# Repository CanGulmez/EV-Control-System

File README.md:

# EV Control System based on BBB (BeagleBone Black)

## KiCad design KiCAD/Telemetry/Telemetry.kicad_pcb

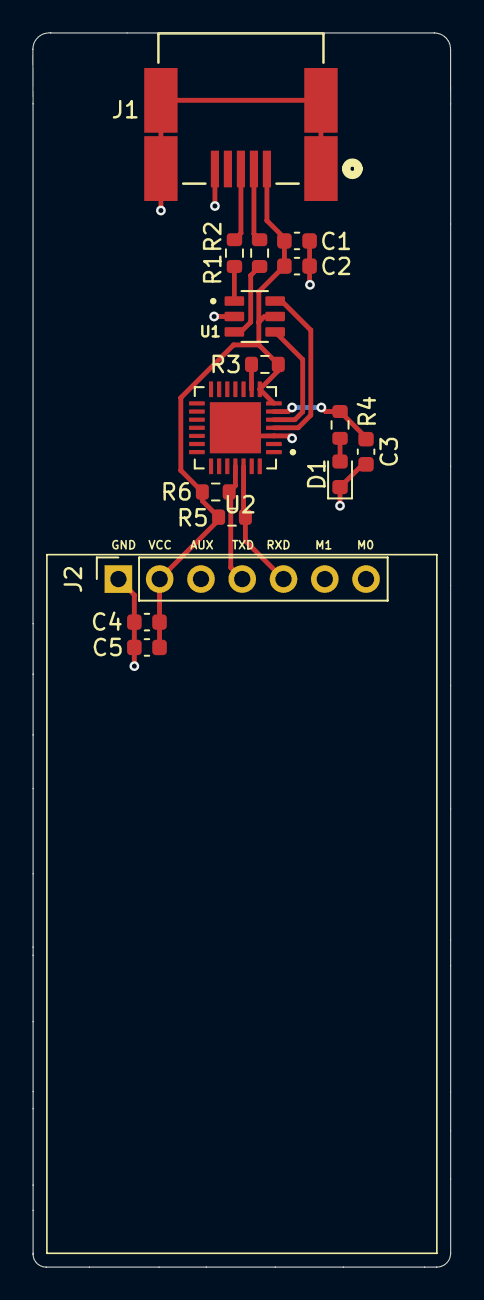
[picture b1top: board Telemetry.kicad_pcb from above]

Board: 2 copper layers, 25.7 x 76.0 mm, 16 parts (0 on the bottom side), 13 nets.

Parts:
C1, C2, C3, C4, C5: 0.1uF; C_0603_1608Metric
D1: LED; LED_0603_1608Metric
J1: 565790576; 56579-0576_MOL
J2: Conn_01x07_Socket; PinSocket_1x07_P2.54mm_Vertical
R1, R2: 22; R_0603_1608Metric
R3, R5, R6: 4k7; R_0603_1608Metric
R4: 220; R_0603_1608Metric
U1: USBLC6-2SC6; SOT95P280X145-6N
U2: CP2102; QFN50P500X500X100-29N

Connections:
/CP_D+: U1.6, U2.4 (D+)
/CP_D-: U1.4, U2.5 (D-)
/RED_LED: C3.1, R4.1, U2.6 (VDD)
/RXD: J2.5, R5.2, U2.26 (TXD)
/TXD: J2.4, R6.2, U2.25 (RXD)
/USB_D+: R2.2, U1.1
/USB_D-: R1.1, U1.3
/VBUS: C1.1, C2.1, C4.2, C5.2, J1.1 (VBUS), J2.2, R3.1, R5.1, R6.1, U1.5, U2.7 (REGIN), U2.8 (VBUS)
GND: C1.2, C2.2, C3.2, C4.1, C5.1, D1.1 (K), J1.5 (GND), J2.1, J2.6, J2.7, U1.2, U2.3 (GND), U2.29 (GND)
unnamed: D1.2 (A), R4.2
unnamed: J1.3 (D+), R2.1
unnamed: J1.2 (D-), R1.2
unnamed: R3.2, U2.9 (~RST)

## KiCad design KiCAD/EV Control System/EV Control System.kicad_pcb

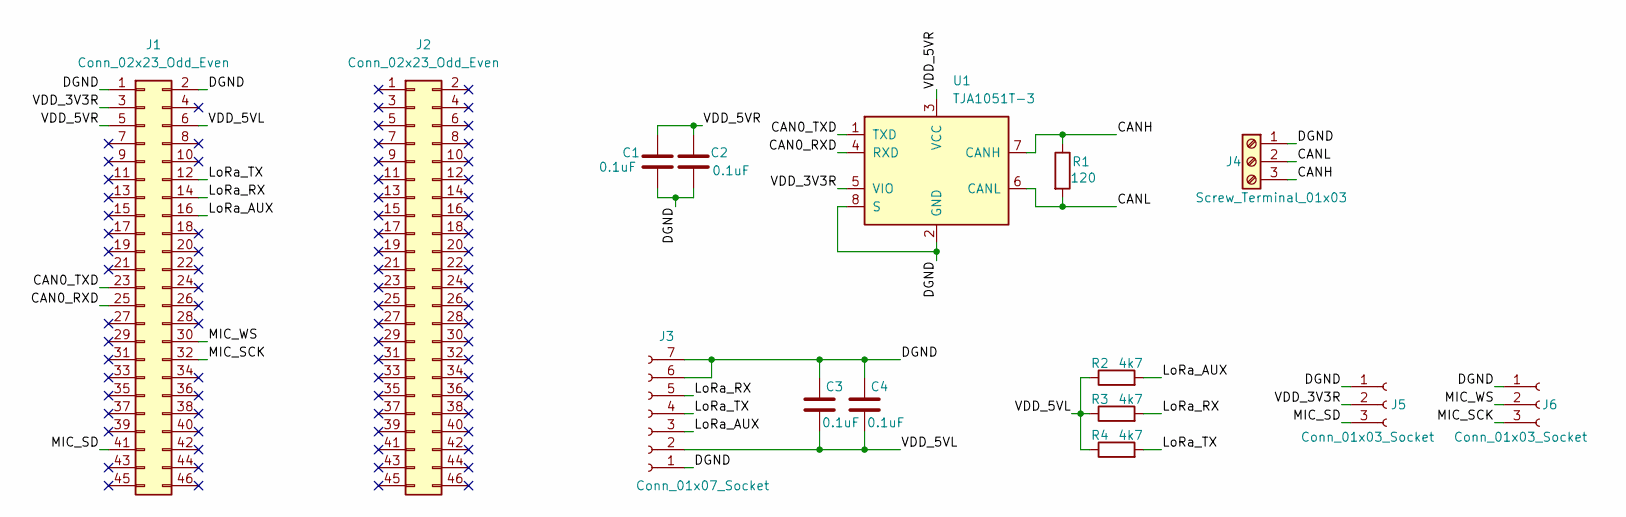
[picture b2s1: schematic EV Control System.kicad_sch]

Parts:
C1, C2, C3, C4: 0.1uF; C_0603_1608Metric
J1, J2: Conn_02x23_Odd_Even; PinHeader_2x23_P2.54mm_Vertical
J3: Conn_01x07_Socket; PinSocket_1x07_P2.54mm_Vertical
J4: Screw_Terminal_01x03; TerminalBlock_Phoenix_MKDS-1,5-3-5.08_1x03_P5.08mm_Horizont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
J5, J6: Conn_01x03_Socket; PinSocket_1x03_P2.54mm_Vertical
R1: 120; R_0603_1608Metric
R2, R3, R4: 4k7; R_0603_1608Metric
U1: TJA1051T-3; SOIC-8_3.9x4.9mm_P1.27mm

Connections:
/CAN0_RXD: J1.25, U1.4 (RXD)
/CAN0_TXD: J1.23, U1.1 (TXD)
/CANH: J4.3, R1.1, U1.7 (CANH)
/CANL: J4.2, R1.2, U1.6 (CANL)
/DGND: C1.2, C2.2, C3.1, C4.1, J1.1, J1.2, J3.1, J3.6, J3.7, J4.1, J5.1, J6.1, U1.2 (GND), U1.8 (S)
/LoRa_AUX: J1.16, J3.3, R2.2
/LoRa_RX: J1.14, J3.5, R3.2
/LoRa_TX: J1.12, J3.4, R4.2
/MIC_SCK: J1.32, J6.3
/MIC_SD: J1.41, J5.3
/MIC_WS: J1.30, J6.2
/VDD_3V3R: J1.3, J5.2, U1.5 (VIO)
/VDD_5VL: C3.2, C4.2, J1.6, J3.2, R2.1, R3.1, R4.1
/VDD_5VR: C1.1, C2.1, J1.5, U1.3 (VCC)

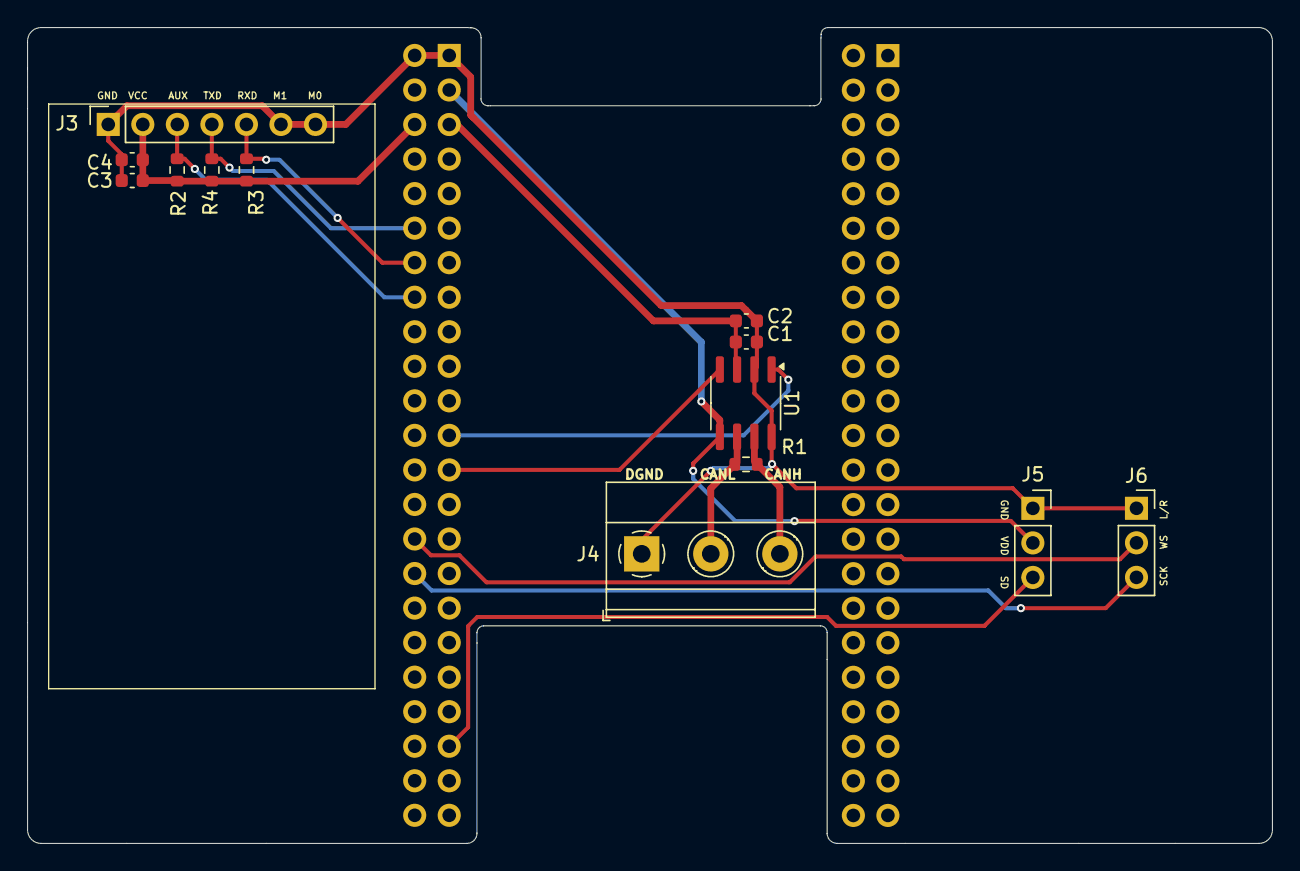
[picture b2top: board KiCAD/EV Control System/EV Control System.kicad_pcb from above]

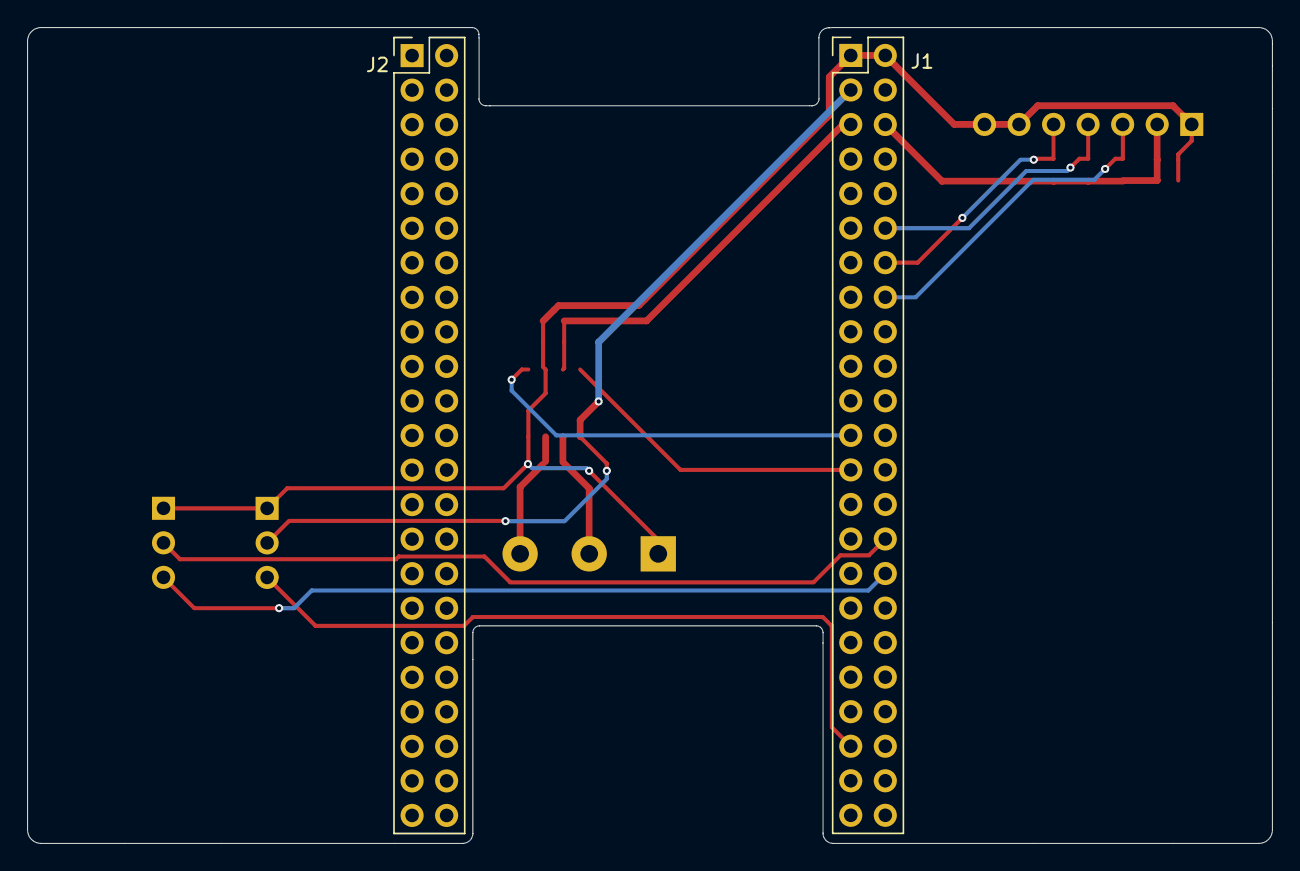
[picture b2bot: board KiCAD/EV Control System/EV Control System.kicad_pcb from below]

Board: 2 copper layers, 91.6 x 60.0 mm, 15 parts (2 on the bottom side), 14 nets.

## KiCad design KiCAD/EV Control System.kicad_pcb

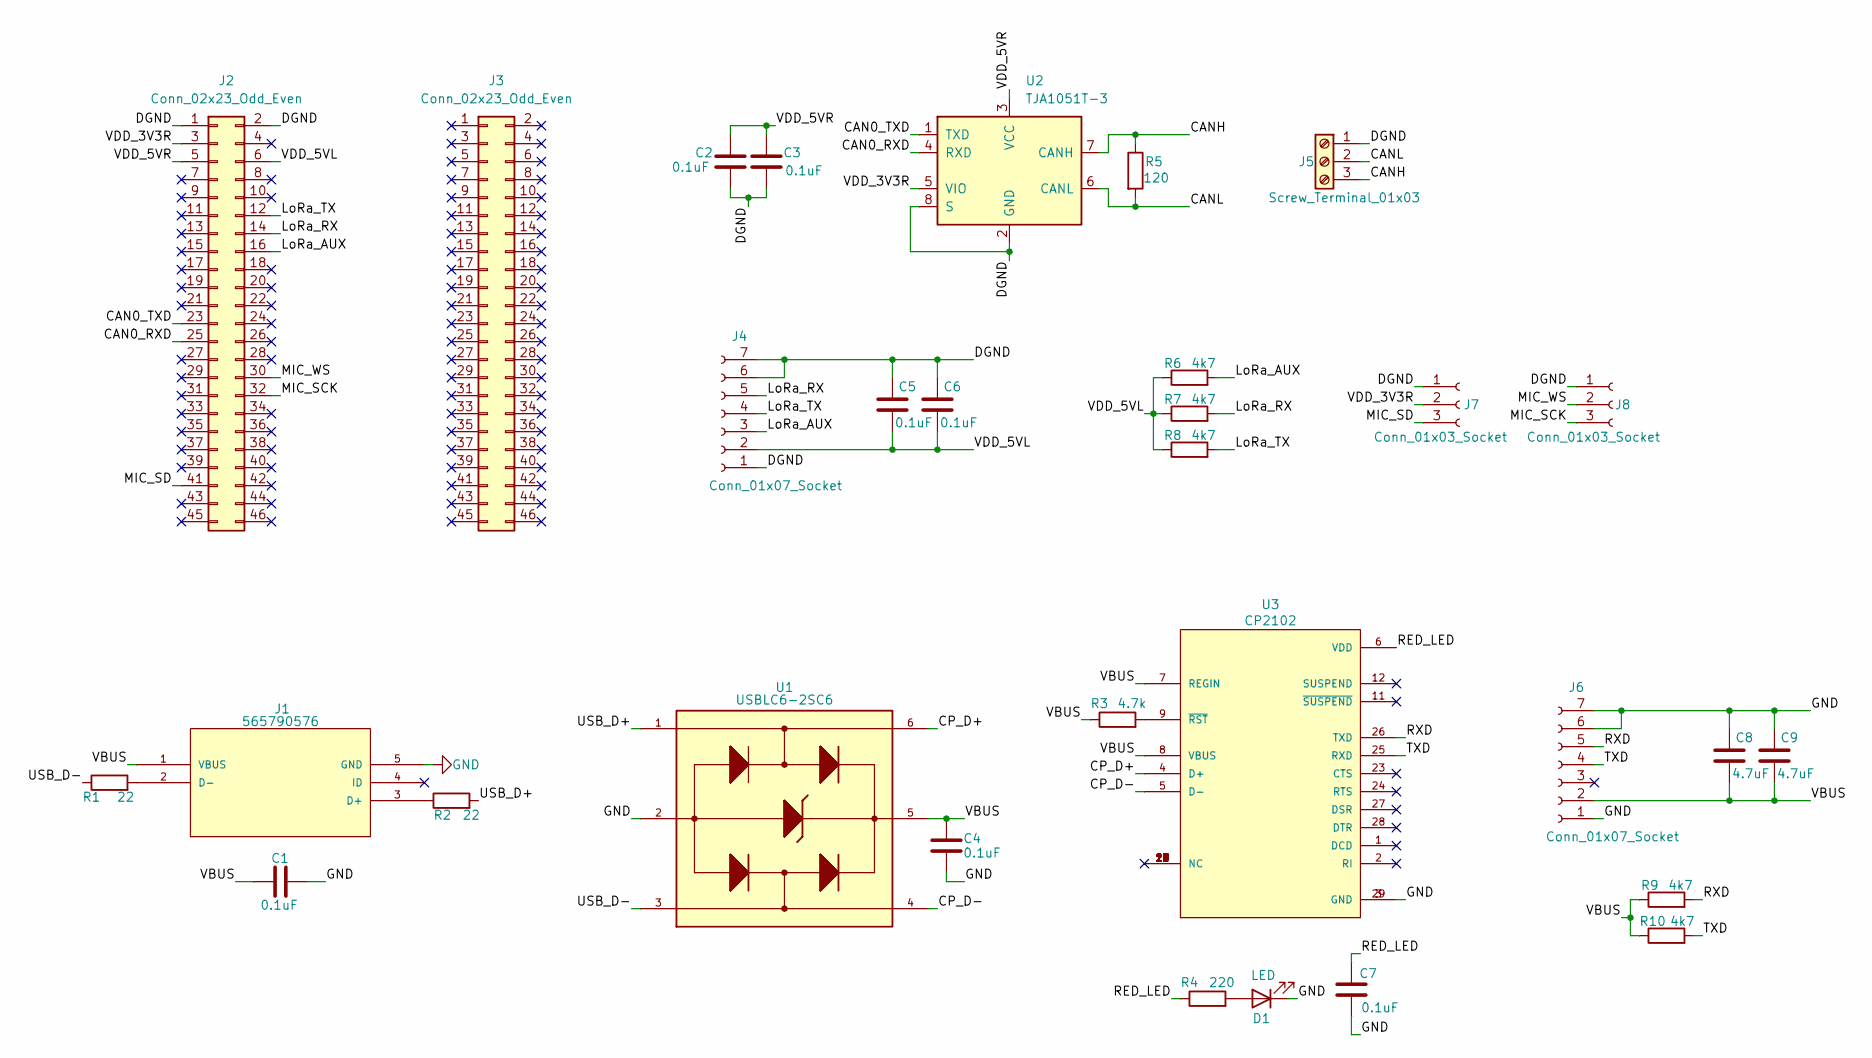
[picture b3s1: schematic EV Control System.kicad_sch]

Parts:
C1, C2, C3, C4, C5, C6, C7: 0.1uF; C_0603_1608Metric
C8, C9: 4.7uF; C_0603_1608Metric
D1: LED; LED_0603_1608Metric
J1: 565790576; 56579-0576_MOL; MANUFACTURER_PART_NUMBER 565790576
J2, J3: Conn_02x23_Odd_Even; PinHeader_2x23_P2.54mm_Vertical
J4, J6: Conn_01x07_Socket; PinSocket_1x07_P2.54mm_Vertical
J5: Screw_Terminal_01x03; TerminalBlock_Phoenix_MKDS-1,5-3-5.08_1x03_P5.08mm_Horizont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
J7, J8: Conn_01x03_Socket; PinSocket_1x03_P2.54mm_Vertical
R1, R2: 22; R_0603_1608Metric
R3: 4.7k; R_0603_1608Metric
R4: 220; R_0603_1608Metric
R5: 120; R_0603_1608Metric
R6, R7, R8, R9, R10: 4k7; R_0603_1608Metric
U1: USBLC6-2SC6; SOT95P280X145-6N
U2: TJA1051T-3; SOIC-8_3.9x4.9mm_P1.27mm
U3: CP2102; QFN50P500X500X100-29N

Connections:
/CAN0_RXD: J2.25, U2.4 (RXD)
/CAN0_TXD: J2.23, U2.1 (TXD)
/CANH: J5.3, R5.1, U2.7 (CANH)
/CANL: J5.2, R5.2, U2.6 (CANL)
/CP_D+: U1.6, U3.4 (D+)
/CP_D-: U1.4, U3.5 (D-)
/DGND: C2.2, C3.2, C5.1, C6.1, J2.1, J2.2, J4.1, J4.6, J4.7, J5.1, J7.1, J8.1, U2.2 (GND), U2.8 (S)
/LoRa_AUX: J2.16, J4.3, R6.2
/LoRa_RX: J2.14, J4.5, R7.2
/LoRa_TX: J2.12, J4.4, R8.2
/MIC_SCK: J2.32, J8.3
/MIC_SD: J2.41, J7.3
/MIC_WS: J2.30, J8.2
/RED_LED: C7.1, R4.1, U3.6 (VDD)
/RXD: J6.5, R9.2, U3.26 (TXD)
/TXD: J6.4, R10.2, U3.25 (RXD)
/USB_D+: R2.2, U1.1
/USB_D-: R1.1, U1.3
/VBUS: C1.1, C4.1, C8.2, C9.2, J1.1 (VBUS), J6.2, R3.1, R9.1, R10.1, U1.5, U3.7 (REGIN), U3.8 (VBUS)
/VDD_3V3R: J2.3, J7.2, U2.5 (VIO)
/VDD_5VL: C5.2, C6.2, J2.6, J4.2, R6.1, R7.1, R8.1
/VDD_5VR: C2.1, C3.1, J2.5, U2.3 (VCC)
GND: C1.2, C4.2, C7.2, C8.1, C9.1, D1.1 (K), J1.5 (GND), J1.6, J1.7, J1.8, J1.9, J6.1, J6.6, J6.7, U1.2, U3.3 (GND), U3.29 (GND)
unnamed: D1.2 (A), R4.2
unnamed: J1.3 (D+), R2.1
unnamed: J1.2 (D-), R1.2
unnamed: R3.2, U3.9 (~RST)

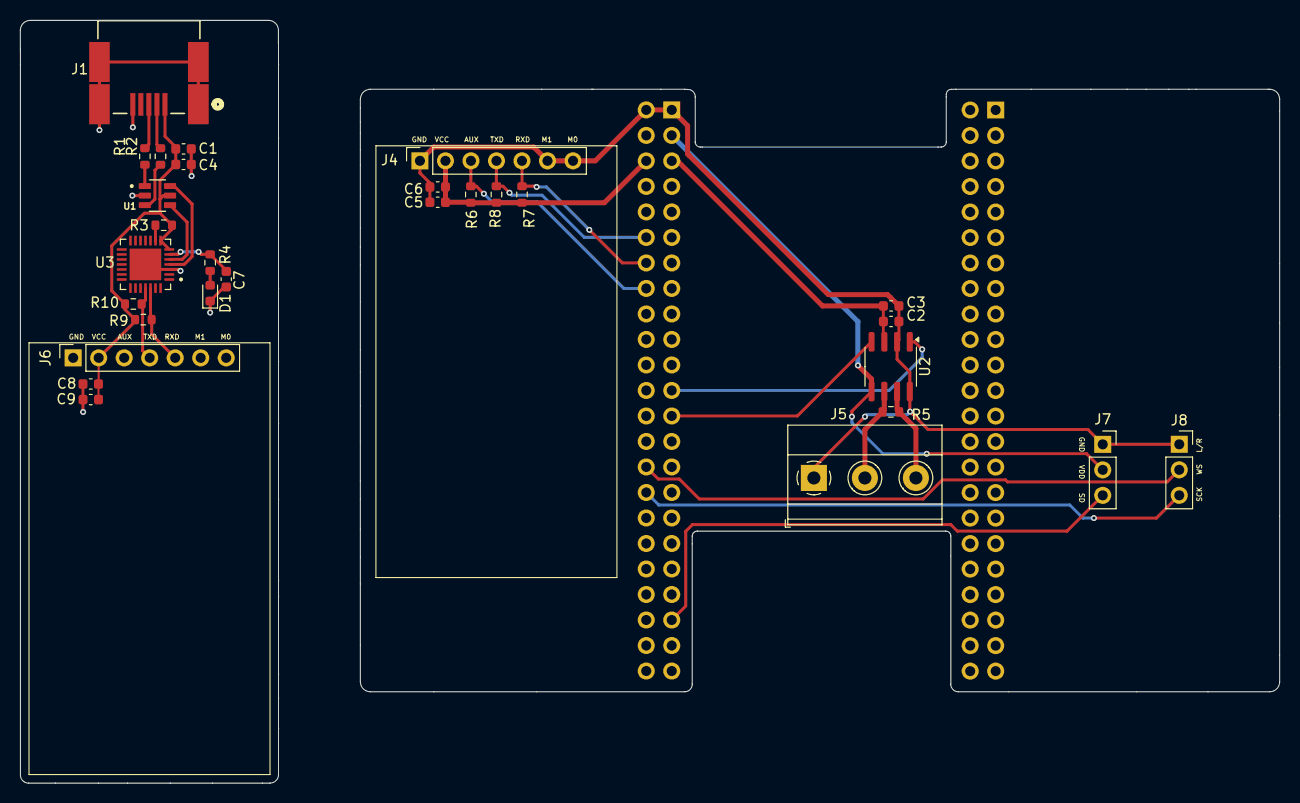
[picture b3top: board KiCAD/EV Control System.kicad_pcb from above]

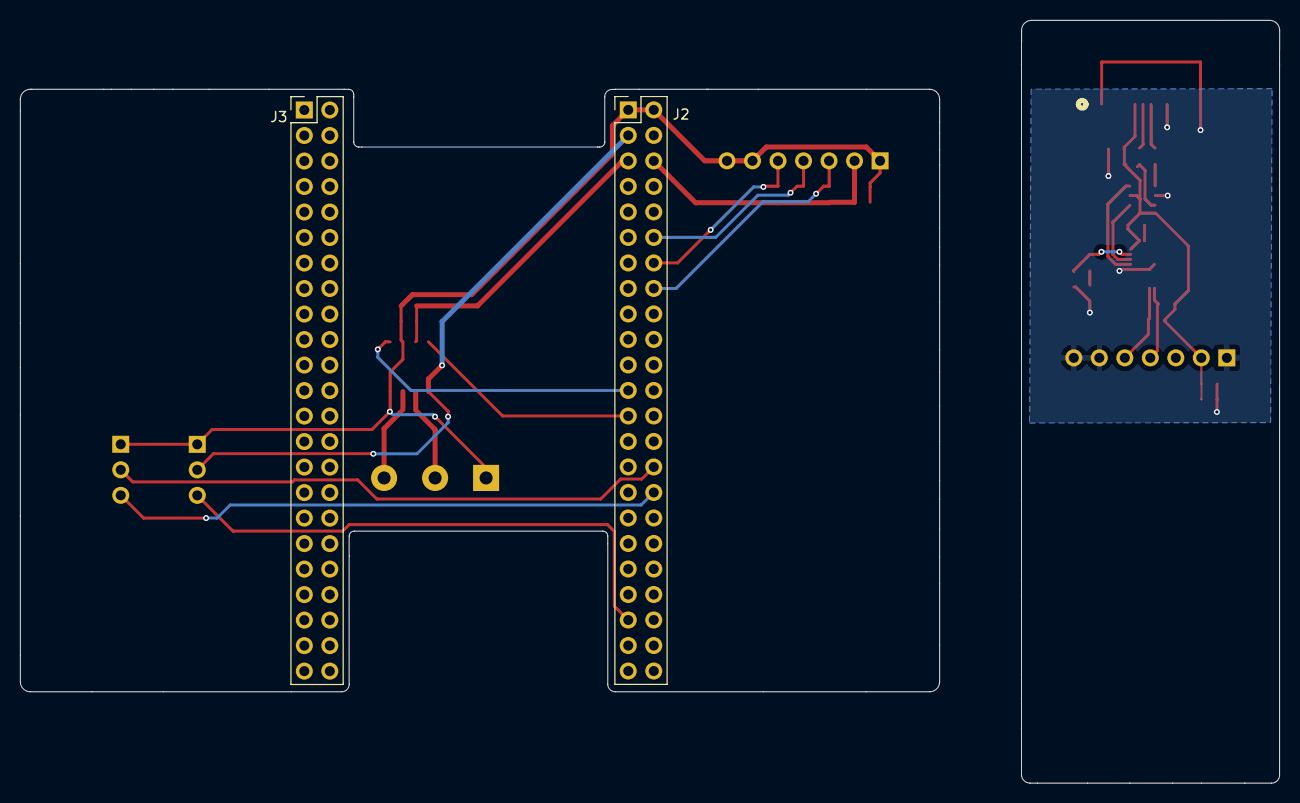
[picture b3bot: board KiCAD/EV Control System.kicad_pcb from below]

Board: 2 copper layers, 125.4 x 76.0 mm, 31 parts (2 on the bottom side), 27 nets.
